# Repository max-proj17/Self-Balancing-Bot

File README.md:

# Self Balancing Bot

Welcome!  

This project has its own dedicated folder and wiki page for documentation, code, and resources.
Click the link below!

[Wiki](https://github.com/max-proj17/Robotics-Projects/wiki)

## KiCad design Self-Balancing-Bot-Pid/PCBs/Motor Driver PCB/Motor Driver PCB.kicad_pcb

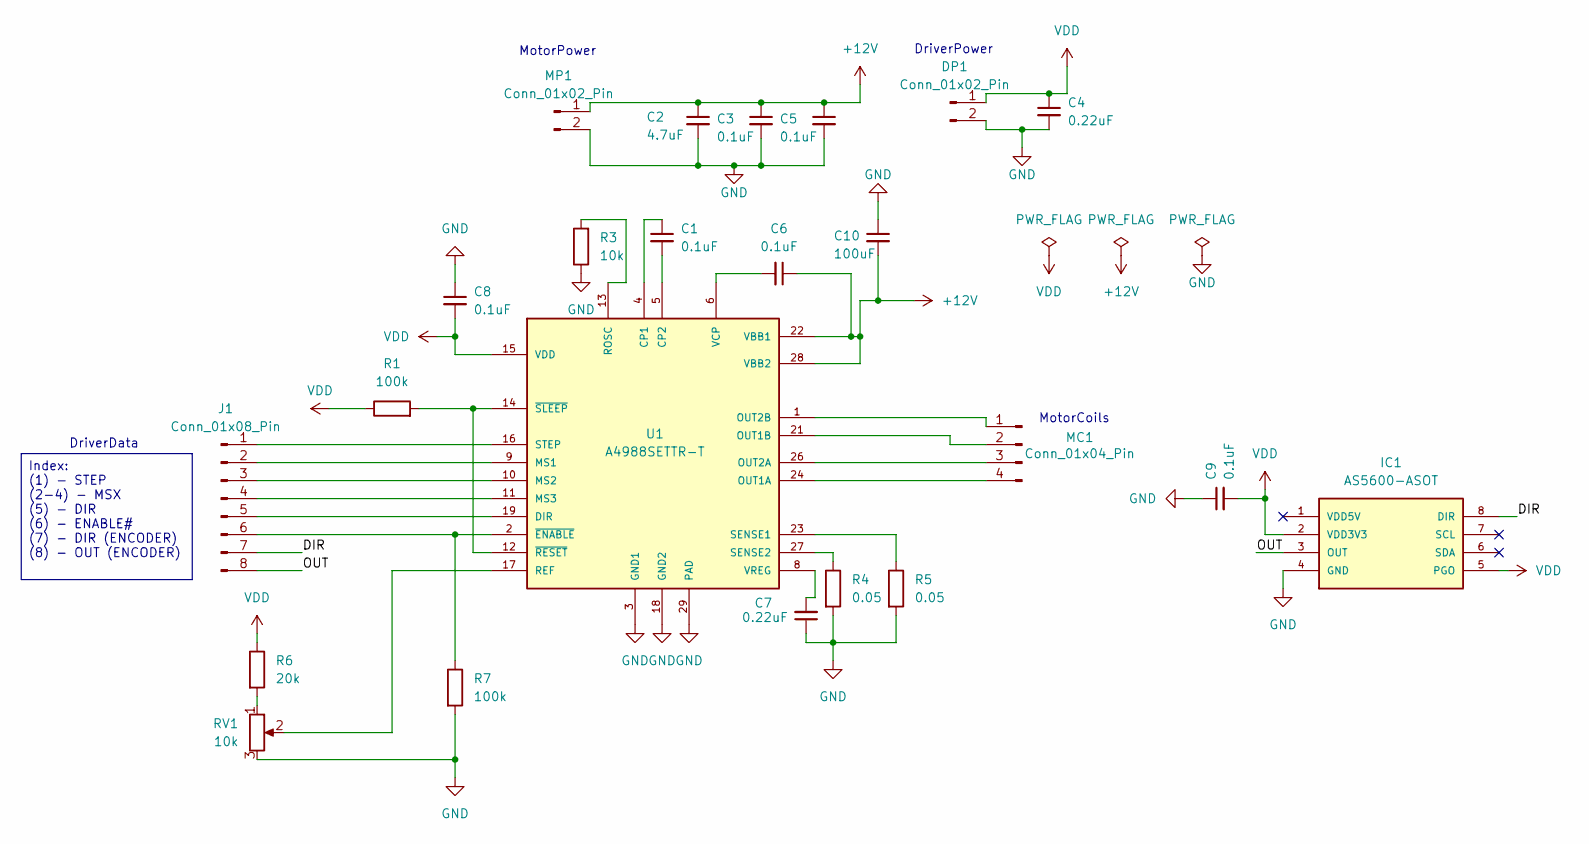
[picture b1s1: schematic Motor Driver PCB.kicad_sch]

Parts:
C1, C3, C5, C8, C9: 0.1uF; C_0603_1608Metric
C2: 4.7uF; C_0603_1608Metric
C4, C7: 0.22uF; C_0603_1608Metric
C6: 0.1uF; C_1210_3225Metric
C10: 100uF; C_0603_1608Metric
DP1: Conn_01x02_Pin; JST_PH_B2B-PH-K_1x02_P2.00mm_Vertical
IC1: AS5600-ASOT; SOIC127P600X175-8N; MOUSER_PART_NUMBER 985-AS5600-ASOT
J1: Conn_01x08_Pin; JST_PH_B8B-PH-K_1x08_P2.00mm_Vertical
MC1: Conn_01x04_Pin; JST_PH_B4B-PH-K_1x04_P2.00mm_Vertical
MP1: Conn_01x02_Pin; JST_PH_B2B-PH-K_1x02_P2.00mm_Vertical
R1, R7: 100k; R_0603_1608Metric
R3: 10k; R_0603_1608Metric
R4, R5: 0.05; R_0603_1608Metric
R6: 20k; R_0603_1608Metric
RV1: 10k; Potentiometer_Bourns_3269W_Vertical
U1: A4988SETTR-T; QFN50P500X500X90-29N

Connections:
+12V: C2.1, C3.1, C5.1, C6.1, C10.2, MP1.1, U1.22 (VBB1), U1.28 (VBB2)
/DIR: IC1.8 (DIR), J1.7
/OUT: IC1.3 (OUT), J1.8
GND: C2.2, C3.2, C4.2, C5.2, C7.1, C8.1, C9.1, C10.1, DP1.2, IC1.4 (GND), MP1.2, R3.1, R4.2, R5.2, R7.2, RV1.3, U1.3 (GND1), U1.18 (GND2), U1.29 (PAD)
unnamed: J1.1, U1.16 (STEP)
unnamed: J1.2, U1.9 (MS1)
unnamed: J1.3, U1.10 (MS2)
unnamed: J1.4, U1.11 (MS3)
unnamed: J1.5, U1.19 (DIR)
unnamed: J1.6, R7.1, U1.2 (~ENABLE)
unnamed: MC1.1, U1.1 (OUT2B)
unnamed: MC1.2, U1.21 (OUT1B)
unnamed: MC1.3, U1.26 (OUT2A)
unnamed: MC1.4, U1.24 (OUT1A)
unnamed: R6.2, RV1.1
unnamed: C1.1, U1.4 (CP1)
unnamed: C1.2, U1.5 (CP2)
unnamed: RV1.2, U1.17 (REF)
unnamed: R3.2, U1.13 (ROSC)
unnamed: R5.1, U1.23 (SENSE1)
unnamed: R4.1, U1.27 (SENSE2)
unnamed: C6.2, U1.6 (VCP)
unnamed: C7.2, U1.8 (VREG)
unnamed: R1.2, U1.12 (~RESET), U1.14 (~SLEEP)
VDD: C4.1, C8.2, C9.2, DP1.1, IC1.2 (VDD3V3), IC1.5 (PGO), R1.1, R6.1, U1.15 (VDD)

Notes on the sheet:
DriverData
MotorPower
DriverPower
MotorCoils
Index: (1) - STEP (2-4) - MSX (5) - DIR (6) - ENABLE# (7) - DIR (ENCODER) (8) - OUT (ENCODER)

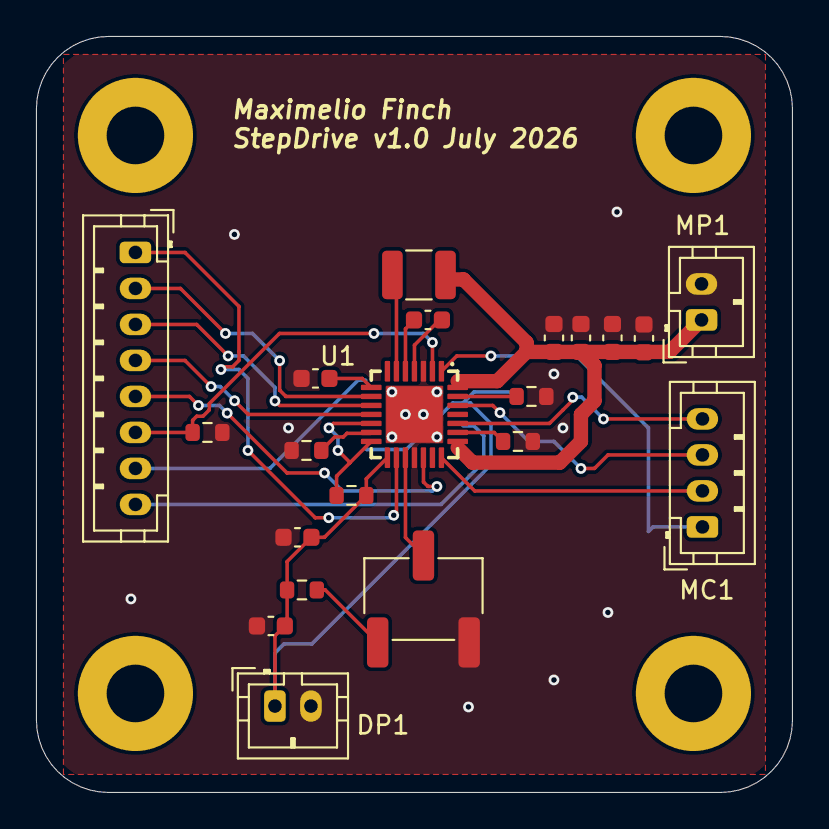
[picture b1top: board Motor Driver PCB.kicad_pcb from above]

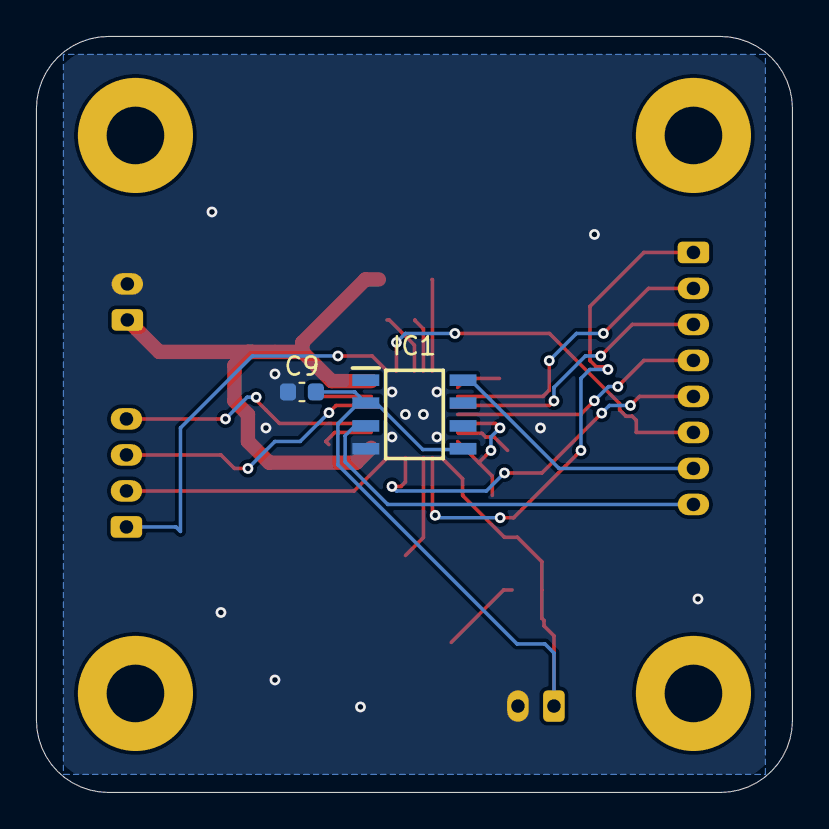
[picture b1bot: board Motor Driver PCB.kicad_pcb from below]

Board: 2 copper layers, 42.0 x 42.0 mm, 27 parts (2 on the bottom side), 25 nets.

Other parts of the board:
Hole1, Hole2, Hole3, Hole4: MountingHole_3.2mm_M3_Pad

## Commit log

2026-04-27 Revise README for Self Balancing Bot project
    Updated project title and modified introductory text.
2026-06-24 Updated gitignore to ignore certain Kicad files. Ran ERC and DRC in Kicad, fixed any remaining issues, and now ready to route.
2026-06-24 Finished initial routing of all traces
